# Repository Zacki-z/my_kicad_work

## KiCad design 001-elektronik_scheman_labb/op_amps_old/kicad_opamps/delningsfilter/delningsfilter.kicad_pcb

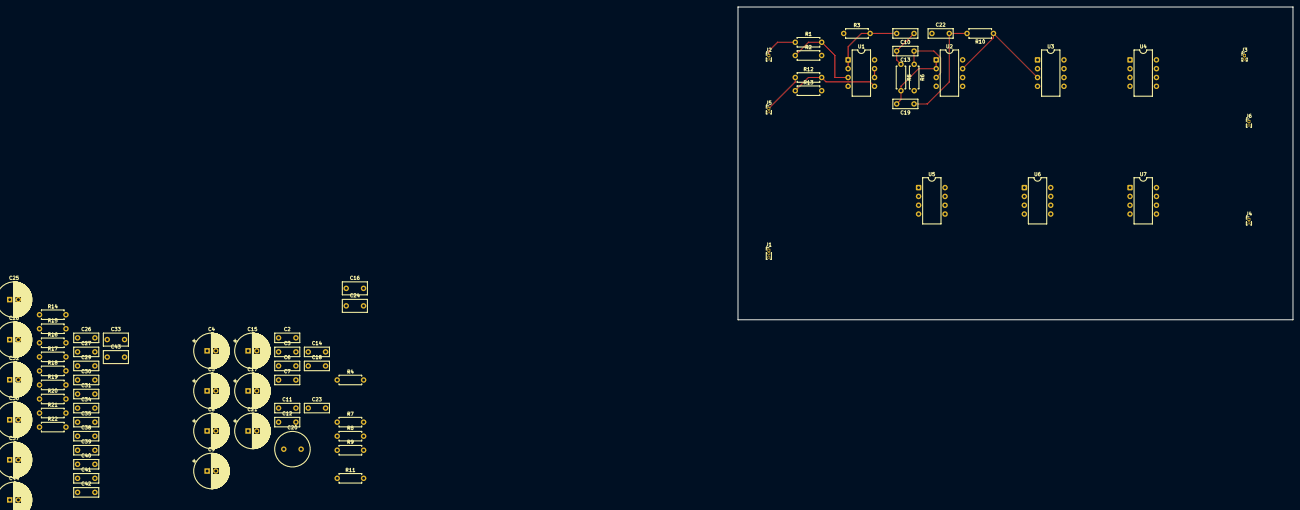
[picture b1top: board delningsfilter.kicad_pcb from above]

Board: 2 copper layers, 160.0 x 90.2 mm, 78 parts (0 on the bottom side), 38 nets.

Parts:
C2, C3, C6, C7, C10, C12, C13, C14, C18, C19, C22, C26, C27, C29, C31, C34, C35, C38, C39, C40, C42: 100nF; C_Rect_L7.0mm_W2.5mm_P5.00mm
C4, C5, C8, C9, C15, C17, C21, C25, C28, C32, C36, C37, C44: 10 uF; CP_Radial_D10.0mm_P2.50mm
C11, C30: 68nF; C_Rect_L7.0mm_W2.5mm_P5.00mm
C16, C24, C33, C43: 150 nF; C_Rect_L7.0mm_W3.5mm_P5.00mm
C20: 100nF; C_Radial_D10.0mm_H12.5mm_P5.00mm
C23, C41: 68 nF; C_Rect_L7.0mm_W2.5mm_P5.00mm
J1: POWER; PinHeader_1x03_P1.00mm_Vertical
J2: Right_in; PinHeader_1x02_P1.00mm_Vertical
J3: Right_out; PinHeader_1x02_P1.00mm_Vertical
J4: LP_out; PinHeader_1x02_P1.00mm_Vertical
J5: LEFT_in; PinHeader_1x02_P1.00mm_Vertical
J6: LEFT_OUT; PinHeader_1x02_P1.00mm_Vertical
R1, R12, R22: 1k; R_Axial_DIN0207_L6.3mm_D2.5mm_P7.62mm_Horizontal
R2, R13: 100k; R_Axial_DIN0207_L6.3mm_D2.5mm_P7.62mm_Horizontal
R3, R4, R7, R8, R14, R15, R18, R19: 19.6k; R_Axial_DIN0207_L6.3mm_D2.5mm_P7.62mm_Horizontal
R5, R10, R11, R16, R21: 28k; R_Axial_DIN0207_L6.3mm_D2.5mm_P7.62mm_Horizontal
R6, R9, R17, R20: 14k; R_Axial_DIN0207_L6.3mm_D2.5mm_P7.62mm_Horizontal
U1, U2, U3, U4, U5, U6, U7: OPA1656ID; CERDIP-8_W7.62mm_SideBrazed

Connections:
+12V: C3.1, C4.1, C7.1, C8.1, C14.1, C15.1, C20.1, C21.1, C27.1, C28.1, C35.1, C36.1, C42.1, C44.1, J1.1, U1.8 (V+), U2.8 (V+), U3.8 (V+), U4.8 (V+), U5.8 (V+), U6.8 (V+), U7.8 (V+)
-12V: C2.1, C5.2, C6.1, C9.2, C12.1, C17.2, C18.1, C25.2, C26.1, C32.2, C34.1, C37.2, C39.1, J1.2, U1.4 (V-), U2.4 (V-), U3.4 (V-), U4.4 (V-), U5.4 (V-), U6.4 (V-), U7.4 (V-)
/LP_OUT: R11.2, U3.6 (-), U3.7
/Left_channel/L_BUF: C29.2, R14.2, U1.6 (-), U1.7
/Left_channel/L_CH_IN: R12.2, R13.1, U1.5 (+)
/Left_channel/L_HP-OUT: J6.1, U7.1, U7.2 (-)
/Left_channel/L_HP_S1: C38.2, R16.2, U6.1, U6.2 (-)
/Left_channel/L_IN: J5.1, R12.1
/Left_channel/L_LP_OUT: R22.2, U7.6 (-), U7.7
/Left_channel/L_LP_S1: C33.1, R18.2, U5.6 (-), U5.7
/Left_channel/L_LP_S2: C43.2, U5.1, U5.2 (-), U7.5 (+)
/Left_channel/l_HP_S2: R21.1, U6.6 (-), U6.7, U7.3 (+)
/R_BUF: C10.2, R3.2, U1.1, U1.2 (-)
/R_CH_IN: R1.2, R2.1, U1.3 (+)
/R_HP-OUT: J3.1, U3.1, U3.2 (-)
/R_HP_S1: C19.2, R5.2, U2.1, U2.2 (-)
/R_HP_S2: R10.1, U2.6 (-), U2.7, U3.3 (+)
/R_IN: J2.1, R1.1
/R_LP_S1: C16.1, R7.2, U4.6 (-), U4.7
/R_LP_S2: C24.2, U3.5 (+), U4.1, U4.2 (-)
COM_LP_OUT: J4.1, R11.1, R22.1
unnamed: C10.1, C13.2, R5.1
unnamed: C16.2, R3.1, R4.2
unnamed: C19.1, C22.2, R10.2
unnamed: C24.1, R7.1, R8.2
unnamed: C29.1, C31.2, R16.1
unnamed: C33.2, R14.1, R15.2
unnamed: C38.1, C40.2, R21.2
unnamed: C43.1, R18.1, R19.2
unnamed: C13.1, R6.1, U2.3 (+)
unnamed: C22.1, R9.1, U2.5 (+)
unnamed: C23.1, R8.1, U4.3 (+)
unnamed: C11.1, R4.1, U4.5 (+)
unnamed: C41.1, R19.1, U5.3 (+)
unnamed: C30.1, R15.1, U5.5 (+)
unnamed: C31.1, R17.1, U6.3 (+)
unnamed: C40.1, R20.1, U6.5 (+)
SIGNAL_GND: C2.2, C3.2, C4.2, C5.1, C6.2, C7.2, C8.2, C9.1, C11.2, C12.2, C14.2, C15.2, C17.1, C18.2, C20.2, C21.2, C23.2, C25.1, C26.2, C27.2, C28.2, C30.2, C32.1, C34.2, C35.2, C36.2, C37.1, C39.2, C41.2, C42.2, C44.2, J1.3, J2.2, J3.2, J4.2, J5.2, J6.2, R2.2, R6.2, R9.2, R13.2, R17.2, R20.2

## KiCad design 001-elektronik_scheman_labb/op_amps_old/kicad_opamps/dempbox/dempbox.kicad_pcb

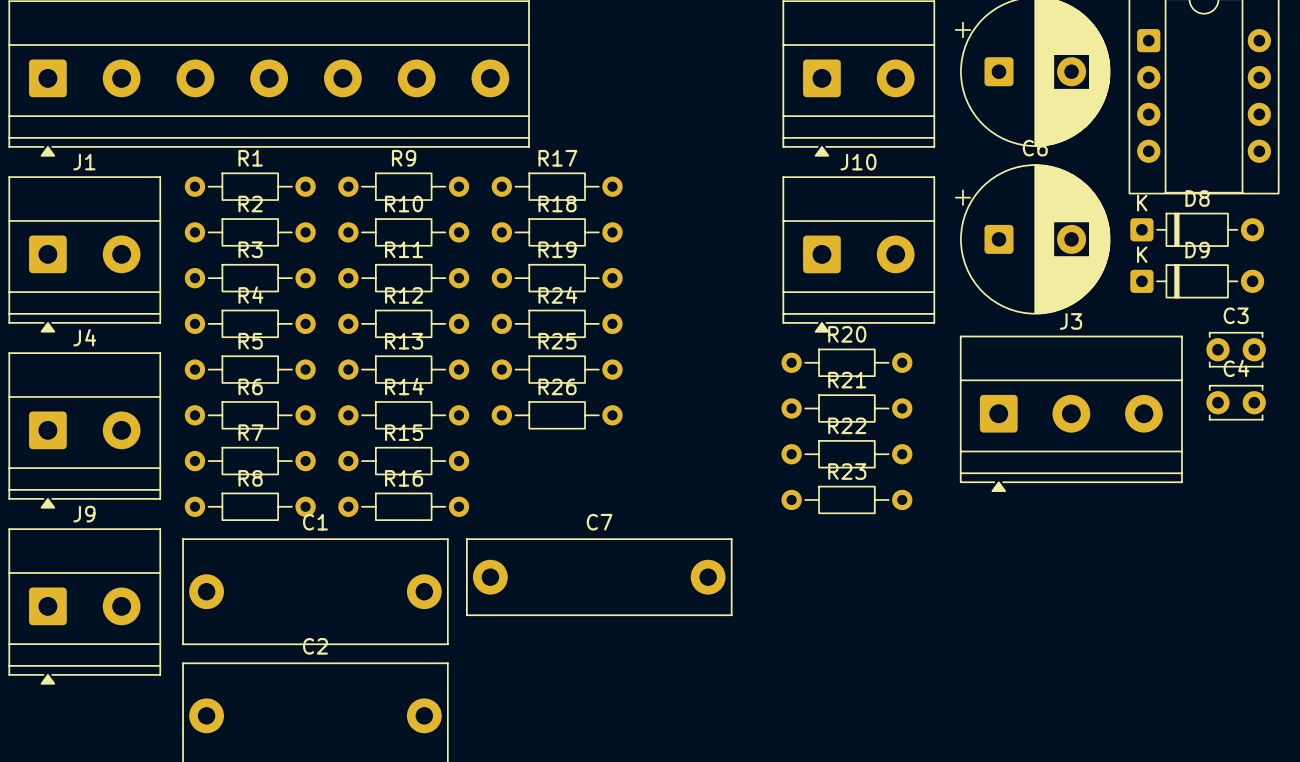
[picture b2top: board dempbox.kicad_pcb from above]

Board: 2 copper layers, 43 parts (0 on the bottom side), 22 nets, no tracks yet.

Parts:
C1, C2: 100 nF 630v; C_Rect_L18.0mm_W7.0mm_P15.00mm_FKS3_FKP3
C3, C4: 100 nF; C_Disc_D3.4mm_W2.1mm_P2.50mm
C5, C6: 10 uF; CP_Radial_D10.0mm_P5.00mm
C7: 100 nF 630V; C_Rect_L18.0mm_W5.0mm_P15.00mm_FKS3_FKP3
D8, D9: BZX55C5V1; D_DO-35_SOD27_P7.62mm_Horizontal
J1: Test_probe; TerminalBlock_Phoenix_MKDS-1,5-2-5.08_1x02_P5.08mm_Horizont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
J2: Focusrite input; TerminalBlock_Phoenix_MKDS-1,5-2-5.08_1x02_P5.08mm_Horizont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
J3: OP_AMP_PWR; TerminalBlock_Phoenix_MKDS-1,5-3_1x03_P5.00mm_Horizontal
J4: Speaker; TerminalBlock_Phoenix_MKDS-1,5-2-5.08_1x02_P5.08mm_Horizont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
J9, J10: Mätinstrument; TerminalBlock_Phoenix_MKDS-1,5-2-5.08_1x02_P5.08mm_Horizont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
J11: J_SW_SIGNAL; TerminalBlock_Phoenix_MKDS-1,5-7-5.08_1x07_P5.08mm_Horizont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
R1: 680; R_Axial_DIN0204_L3.6mm_D1.6mm_P7.62mm_Horizontal
R2, R3, R4, R5, R6, R8, R17: 1k; R_Axial_DIN0204_L3.6mm_D1.6mm_P7.62mm_Horizontal
R7, R12, R21, R26: 1M; R_Axial_DIN0204_L3.6mm_D1.6mm_P7.62mm_Horizontal
R9, R13: 953k; R_Axial_DIN0204_L3.6mm_D1.6mm_P7.62mm_Horizontal
R10: 19,6K; R_Axial_DIN0204_L3.6mm_D1.6mm_P7.62mm_Horizontal
R11, R16, R23: 100k; R_Axial_DIN0204_L3.6mm_D1.6mm_P7.62mm_Horizontal
R14: 215k; R_Axial_DIN0204_L3.6mm_D1.6mm_P7.62mm_Horizontal
R15: 8 50W; R_Axial_DIN0204_L3.6mm_D1.6mm_P7.62mm_Horizontal
R18: 90,9k; R_Axial_DIN0204_L3.6mm_D1.6mm_P7.62mm_Horizontal
R19: 10k; R_Axial_DIN0204_L3.6mm_D1.6mm_P7.62mm_Horizontal
R20: 20k; R_Axial_DIN0204_L3.6mm_D1.6mm_P7.62mm_Horizontal
R22: 2,2k; R_Axial_DIN0204_L3.6mm_D1.6mm_P7.62mm_Horizontal
R24, R25: 10K; R_Axial_DIN0204_L3.6mm_D1.6mm_P7.62mm_Horizontal
U2: OPA134; CERDIP-8_W7.62mm_SideBrazed_Socket

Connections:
/INT_1_10_OUT: J11.3, R13.2, R14.1
/INT_1_100_OUT: J11.2, R9.2, R10.1
/INT_1_100_OUT-2: C1.2, R9.1
/INT_1_100_OUT-3: C1.1, J1.2, J9.2, R7.1, R7.2, R12.1, R24.2
/LOW_1_1_OUT: J11.6, R25.1, R26.2
/SPK_1_10_OUT: J11.5, R18.2, R19.1
/SPK_1_100_OUT: J11.4, R16.2, R17.1
/SW_COMMON_OUT: J11.7, R8.1
/sound-card/12V+: C3.1, C5.2, J3.2, U2.7 (V+)
/sound-card/12V-: C4.1, C6.1, J3.1, U2.4 (V-)
/sound-card/ATTEN_GND: C3.2, C4.2, C5.1, C6.2, D9.1 (K), J1.1, J2.2, J3.3, J9.1, J10.2, R10.2, R11.1, R14.2, R21.2, R23.2, R26.1
/sound-card/ATTEN_OUT: R8.2, R11.2, R20.2
/sound-card/OP_AMP_OUT: R22.2, U2.2 (-), U2.6
/sound-card/audio out: D8.1 (K), J2.1, J10.1, R22.1, R23.1
unnamed: C2.1, R12.2
unnamed: C2.2, R13.1
unnamed: C7.1, R25.2
unnamed: C7.2, R24.1
unnamed: D8.2 (A), D9.2 (A)
unnamed: J4.1, R15.1, R17.2, R19.2
unnamed: J4.2, R15.2, R16.1, R18.1
unnamed: R20.1, R21.1, U2.3 (+)

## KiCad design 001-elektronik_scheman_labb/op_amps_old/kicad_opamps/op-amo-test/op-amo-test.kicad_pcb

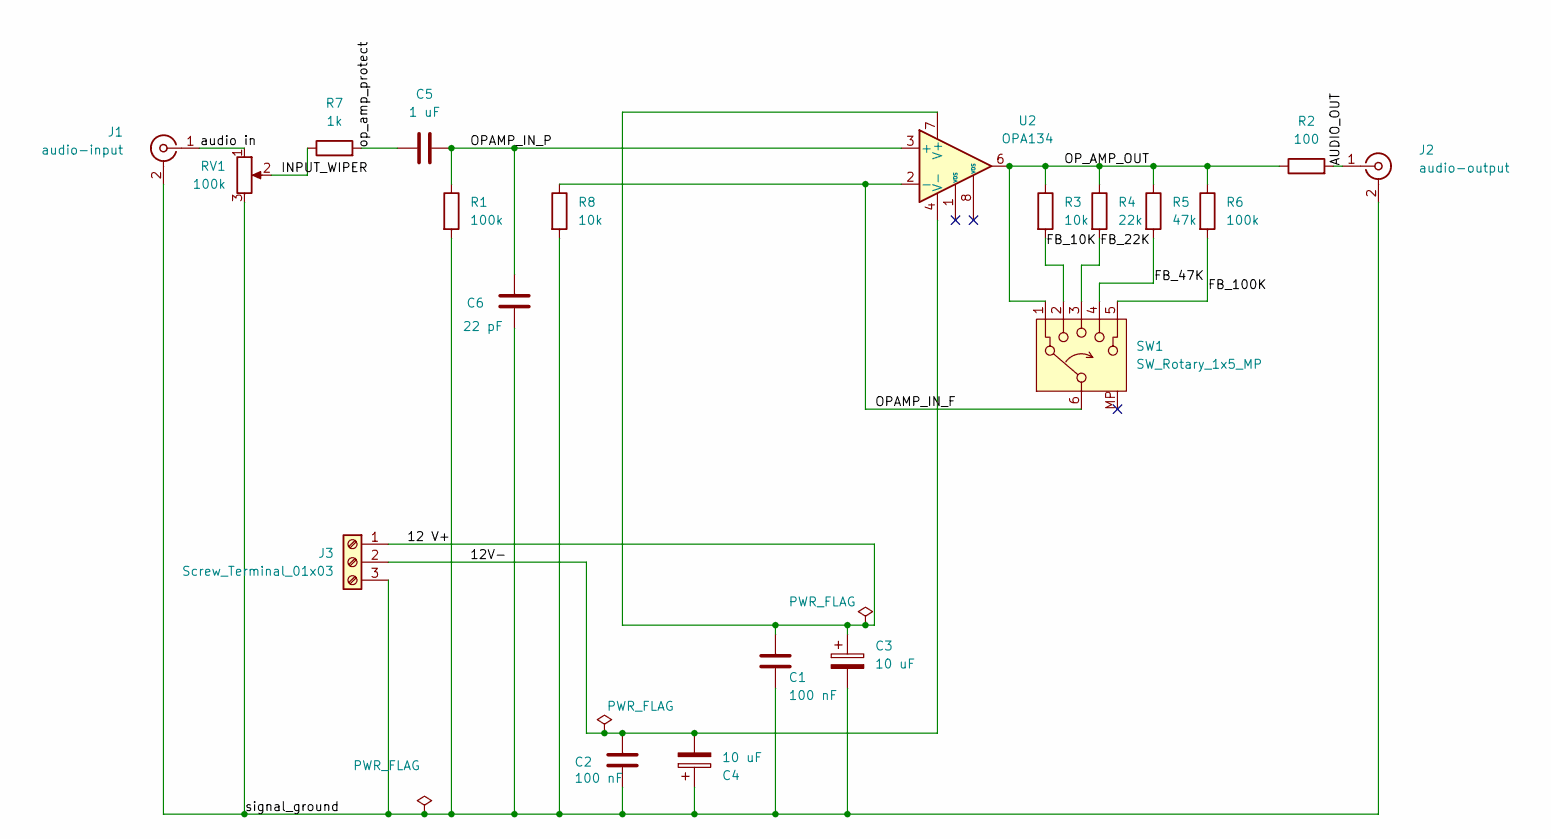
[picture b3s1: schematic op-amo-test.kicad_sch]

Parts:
C1, C2: 100 nF; C_Disc_D5.0mm_W2.5mm_P5.00mm
C3, C4: 10 uF; CP_Radial_D5.0mm_P2.00mm
C5: 1 uF; C_Axial_L12.0mm_D9.5mm_P15.00mm_Horizontal
C6: 22 pF; C_Disc_D7.5mm_W5.0mm_P5.00mm
J1: audio-input; TerminalBlock_MaiXu_MX126-5.0-02P_1x02_P5.00mm
J2: audio-output; TerminalBlock_MaiXu_MX126-5.0-02P_1x02_P5.00mm
J3: Screw_Terminal_01x03; TerminalBlock_MaiXu_MX126-5.0-03P_1x03_P5.00mm
R1, R6: 100k; R_Axial_DIN0207_L6.3mm_D2.5mm_P7.62mm_Horizontal
R2: 100; R_Axial_DIN0207_L6.3mm_D2.5mm_P7.62mm_Horizontal
R3, R8: 10k; R_Axial_DIN0207_L6.3mm_D2.5mm_P7.62mm_Horizontal
R4: 22k; R_Axial_DIN0207_L6.3mm_D2.5mm_P7.62mm_Horizontal
R5: 47k; R_Axial_DIN0207_L6.3mm_D2.5mm_P7.62mm_Horizontal
R7: 1k; R_Axial_DIN0207_L6.3mm_D2.5mm_P7.62mm_Horizontal
RV1: 100k; TerminalBlock_MaiXu_MX126-5.0-03P_1x03_P5.00mm
SW1: SW_Rotary_1x5_MP; TerminalBlock_Xinya_XY308-2.54-6P_1x06_P2.54mm_Horizontal
U2: OPA134; DIP-8_W7.62mm

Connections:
/12 V+: C1.1, C3.1, J3.1, U2.7 (V+)
/12V-: C2.1, C4.2, J3.2, U2.4 (V-)
/AUDIO_OUT: J2.1 (In), R2.2
/FB_10K: R3.2, SW1.2
/FB_22K: R4.2, SW1.3
/FB_47K: R5.2, SW1.4
/FB_100K: R6.2, SW1.5
/INPUT_WIPER: R7.1, RV1.2
/OPAMP_IN_F: R8.1, SW1.6, U2.2 (-)
/OPAMP_IN_P: C5.1, C6.1, R1.1, U2.3 (+)
/OP_AMP_OUT: R2.1, R3.1, R4.1, R5.1, R6.1, SW1.1, U2.6
/audio in: J1.1 (In), RV1.1
/op_amp_protect: C5.2, R7.2
/signal_ground: C1.2, C2.2, C3.2, C4.1, C6.2, J1.2 (Ext), J2.2 (Ext), J3.3, R1.2, R8.2, RV1.3

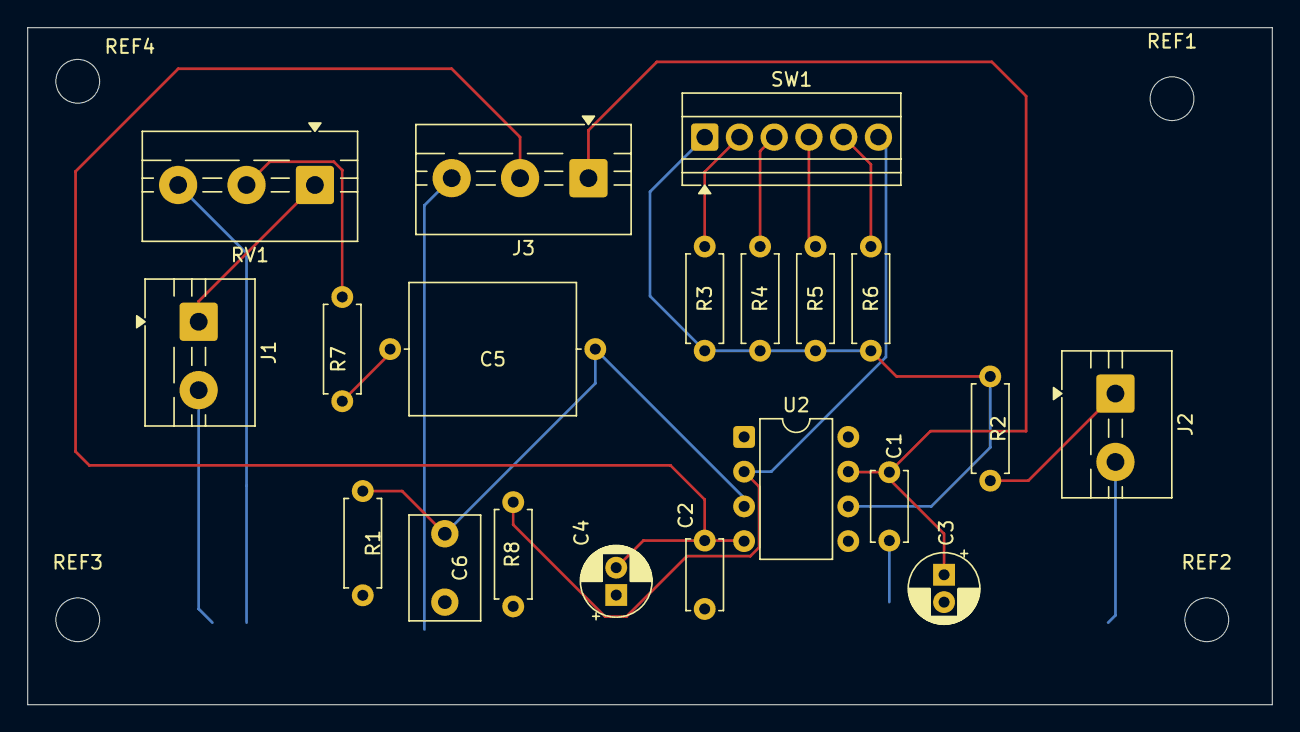
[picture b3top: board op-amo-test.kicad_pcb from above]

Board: 2 copper layers, 91.0 x 49.5 mm, 24 parts (0 on the bottom side), 14 nets.

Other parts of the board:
REF1, REF2, REF3, REF4: MountingHole_3.2mm_M3
